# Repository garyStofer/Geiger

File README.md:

# Geiger Counter module for Air-LCD-Uino

This is a re-implementation of a Geiger counter device, based on [http://rhelectronics.net](http://rhelectronics.net) original work. See link for all the features. 

The PCB is implemented as a daughter module for the back of the AIR-LCD main board. Sources and CAD files are on [GIThub](https://github.com/garyStofer/AIR_LCDuino), PCBs can be ordered from: 

<a href="https://oshpark.com/shared_projects/kT6TDwLU"></img></a>

----------

It uses a Geiger Mueller tube to count, display and record radioactive strikes. 

The device can be operated from 12V using the built in 5V regulator of the main board, or from 4 NiMH batteries by removing the voltage regulator and feeding the battery voltage directly. The Arduino script has a crude High Voltage regulation loop that keeps the Anode voltage in the operation limits of the tube during the decay of the battery voltage. 

Some tuning of the code is required for best operation. 
Specifically the Anode voltage needs to be adjusted for the GM tube chosen, usually around 400V. A 10 to 100Gohm resistor divider needs to be used in order to measure the voltage.  

With attached USB?UART converter the device provides data to a PC tool from RH-Electronics to monitor and graph the readings.

Bare PCB can be ordered from OSH PCB:

<a href="https://oshpark.com/shared_projects/8asBUqMk"></img></a>

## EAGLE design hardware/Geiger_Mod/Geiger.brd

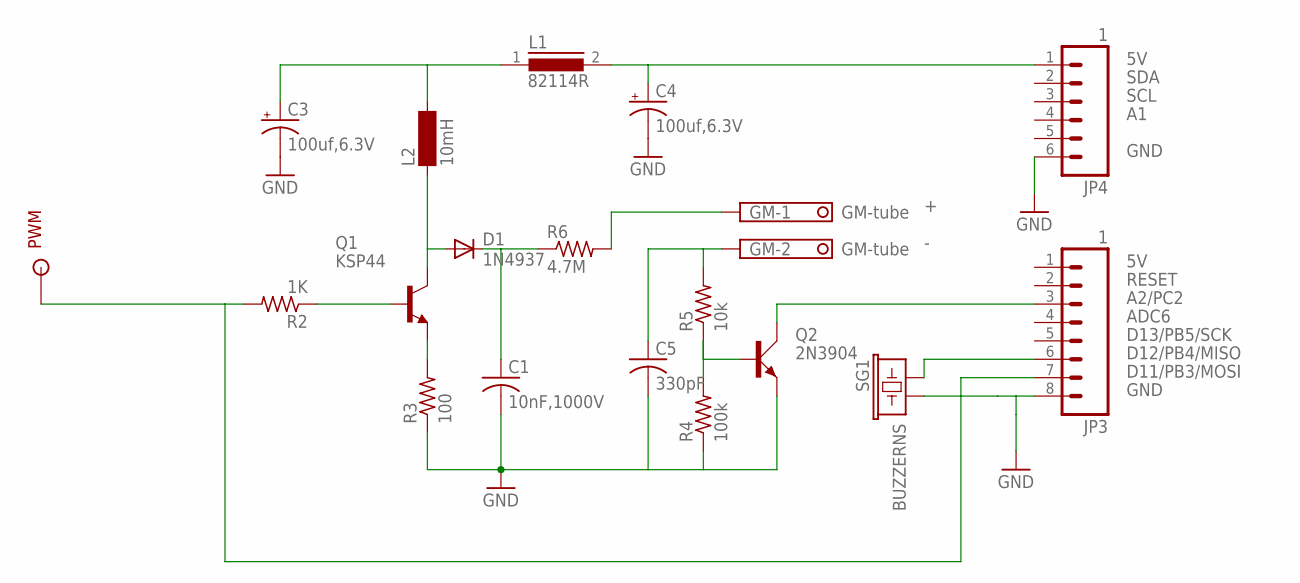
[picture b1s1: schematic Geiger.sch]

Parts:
C1: 10nF,1000V; C150-054X183
C3, C4: 100uf,6.3V; E2,5-7
C5: 330pF; C050-045X075
D1: 1N4937; DO41-10
GM: GM-tube; 1751248
JP3: 1; 1X08
JP4: 1; 1X06
L1: 82114R
L2: 10mH; BS11
PWM: SOLDER_POINTA; P1-13
Q1: KSP44; TO92-CBE
Q2: 2N3904; TO92D
R2: 1K; 0207/10
R3: 100; 0207/10
R4: 100k; 0207/10
R5: 10k; 0207/10
R6: 4.7M; 0207/10
SG1: BUZZERNS; BUZZER-12MM-NS

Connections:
+5V: C4.+, JP4.1, L1.2
GND: C1.2, C3.-, C4.-, C5.2, JP3.8, JP4.6, Q2.E, R3.1, R4.1, SG1.- (2)
unnamed: JP3.7, PWM.1, R2.2
unnamed: Q1.B, R2.1
unnamed: JP3.6, SG1.+ (1)
unnamed: Q1.E, R3.2
unnamed: D1.A, L2.1, Q1.C
unnamed: C1.1, D1.C, R6.1
unnamed: GM.1, R6.2
unnamed: Q2.B, R4.2, R5.1
unnamed: C3.+, L1.1, L2.2
unnamed: C5.1, GM.2, R5.2
RESET: JP3.3, Q2.C

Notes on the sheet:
SDA
SCL
GND
A2/PC2
ADC6
D13/PB5/SCK
D12/PB4/MISO
D11/PB3/MOSI

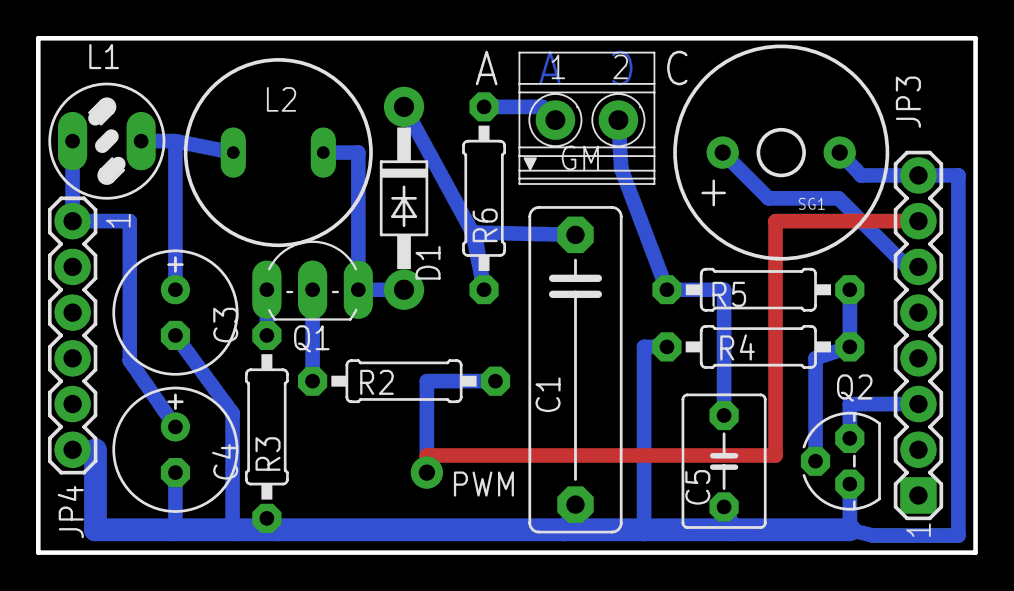
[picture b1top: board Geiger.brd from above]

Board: 2 copper layers, 52.1 x 28.6 mm, 19 parts (0 on the bottom side), 13 nets.

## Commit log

2016-03-21 initial
2016-04-05 Fixed Silk Screen for Q1 being wrong
2016-04-05 updated OSH pcb orderlink in README.md
2016-12-13 added instruction text for burning bootloader via AVR_JTAGICE MK2
2017-02-02 added schematic in PDF form added links to AIR_lcduino in the readme.md file

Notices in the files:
parts and their libraries:
SparkFun-Connectors: Licensing: CC v3.0 Share-Alike You are welcome to use this library for commercial purposes.
